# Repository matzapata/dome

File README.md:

# DOME IOT

IOT modular system to control electrical connections over Wi-Fi.
The projects consists of:
- Modular hardware built with Esp8266 and programmed with C++ that will be placed in electrical sockets
- Phone application built with React Native and expo to connect devices, control them and add family members to it. 

The figma designs are already built and can be found here: 
-  https://www.figma.com/file/vcR1ODs3bJzUiS0fuz7EVW/DOME?node-id=1102%3A9203

## Device setup

1. Create `dome-device/Secrets.h` and fill with firebase credentials

```
#define FIREBASE_HOST "..."
#define FIREBASE_RTDB_SECRET "..." 
```

2. Upload code

3. Make electrical connections and power device on

4. Reset device and keep setup button pressed

5. Connect to "DOME" network initiated by device

6. Make a `POST` to `http://192.168.4.1/set` with `ssid`, `pass`, `home_id` and `device_id` on the body of the request.

```curl
curl --location --request POST 'http://192.168.4.1/set' \
--header 'Content-Type: application/json' \
--data-raw '{
    "ssid": "...",
    "pass": "...",
    "home_id": "...",
    "device_id": "..."
}'
```

If everything is ok, device will respond with `200 "OK"`

7. That's all. Reconect your phone to your wifi and interact with the device

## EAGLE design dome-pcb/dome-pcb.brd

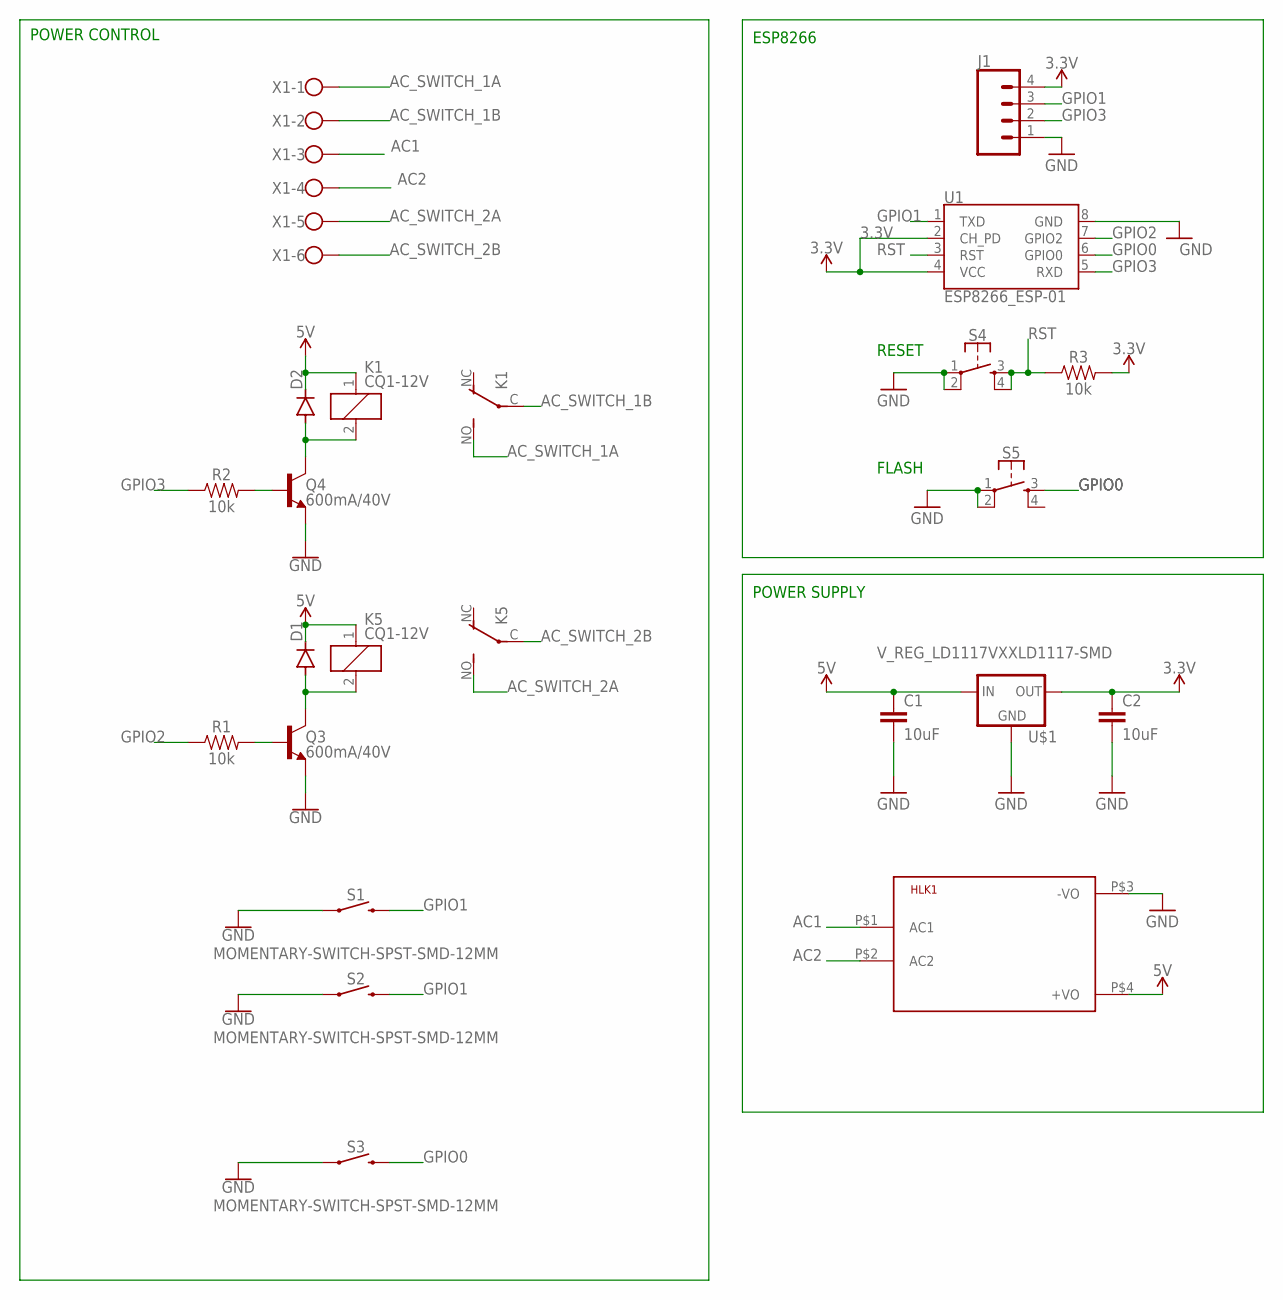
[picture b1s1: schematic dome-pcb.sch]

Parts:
C1, C2: 10uF; 0603
D1, D2: DIODE-DO-214AC; DO-214AC
HLK1: HLK-PM013W; HLK-PM01
J1: CONN_04PTH; 1X04
K1, K5: CQ1-12V; CQ1
Q3, Q4: 600mA/40V; SOT23-3
R1, R2, R3: 10k; 0603
S1, S2, S3: MOMENTARY-SWITCH-SPST-SMD-12MM; TACTILE_SWITCH_SMD_12MM
S4, S5: MOMENTARY-SWITCH-SPST-2-SMD-5.2MM; TACTILE_SWITCH_SMD_5.2MM
U1: ESP8266_ESP-01
U$1: V_REG_LD1117VXXLD1117-SMD; SOT223
X1: W237-6

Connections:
3.3V: C2.1, J1.4, R3.2, U1.2 (CH_PD), U1.4 (VCC), U$1.2 (OUT)
5V: C1.1, D1.C, D2.C, HLK1.P$4 (+VO), K1.1, K5.1, U$1.3 (IN)
AC1: HLK1.P$1 (AC1), X1.3
AC2: HLK1.P$2 (AC2), X1.4
AC_SWITCH_1A: K1.NO (S), X1.1
AC_SWITCH_1B: K1.C, X1.2
AC_SWITCH_2A: K5.NO (S), X1.5
AC_SWITCH_2B: K5.C, X1.6
GND: C1.2, C2.2, HLK1.P$3 (-VO), J1.1, Q3.2 (E), Q4.2 (E), S1.1, S2.1, S3.1, S4.1, S4.2, S5.1, S5.2, U1.8 (GND), U$1.1 (GND)
GPIO0: S3.3 (2), S5.3, U1.6 (GPIO0)
GPIO1: J1.3, S1.3 (2), S2.3 (2), U1.1 (TXD)
GPIO2: R1.1, U1.7 (GPIO2)
GPIO3: J1.2, R2.1, U1.5 (RXD)
unnamed: D2.A, K1.2, Q4.3 (C)
unnamed: Q4.1 (B), R2.2
unnamed: D1.A, K5.2, Q3.3 (C)
unnamed: Q3.1 (B), R1.2
RST: R3.1, S4.3, S4.4, U1.3 (RST)

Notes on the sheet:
FLASH
RESET
POWER CONTROL
ESP8266
POWER SUPPLY

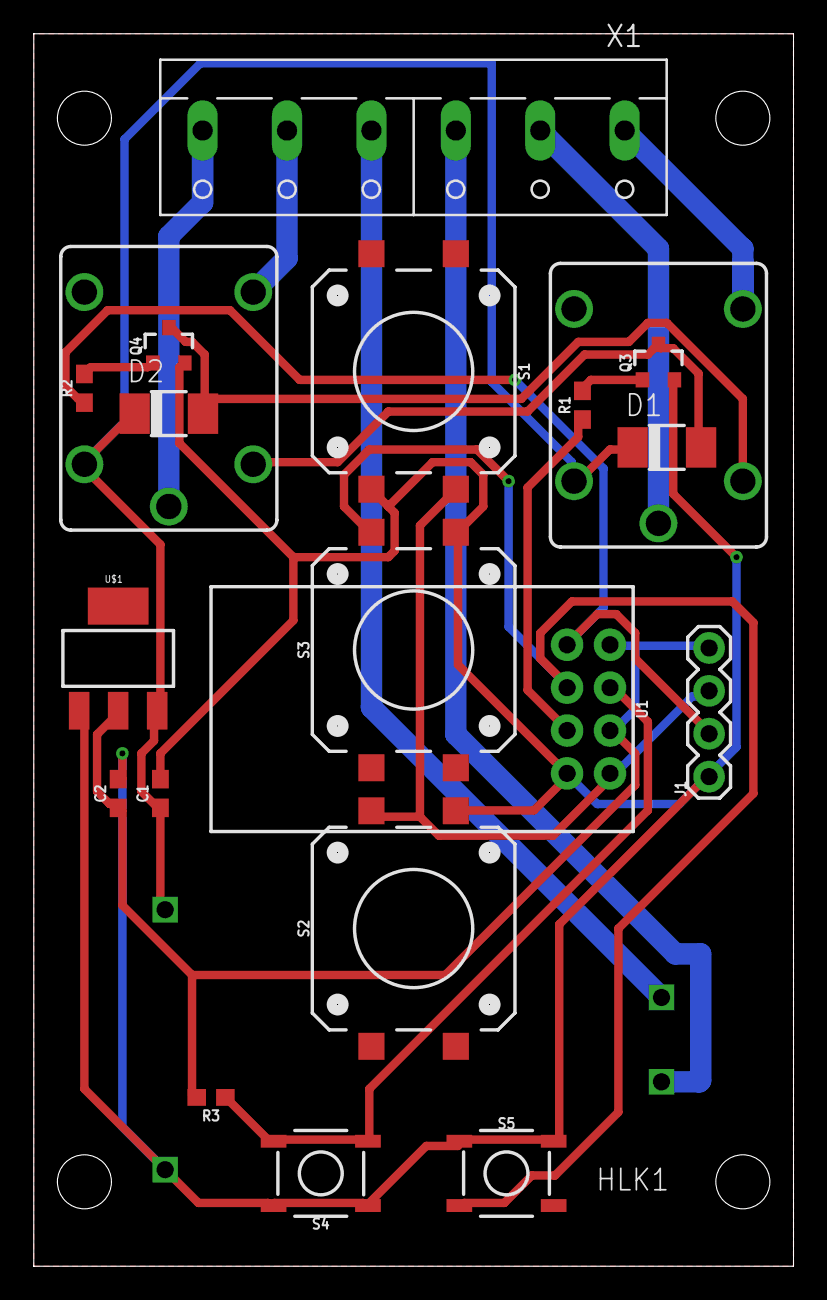
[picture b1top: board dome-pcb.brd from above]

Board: 2 copper layers, 45.0 x 73.0 mm, 21 parts (0 on the bottom side), 18 nets.

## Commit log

2022-10-07 IOT functional connection management system
2022-10-13 Firebase RTDB and buttons integration
2022-10-13 connection manager fixes
2022-10-13 Comment firebase esp version
2022-10-13 Setup NativeWind
2022-10-14 Auth pages UI
2022-10-14 Firebase integration
2022-10-15 UI Screens
2022-10-15 Initialize redux
2022-10-15 Switch Card
2022-10-15 Switches home rendering
2022-10-15 Functional prompt component
2022-10-15 Prompt component
2022-10-17 Share dome qr code generation
2022-10-17 Join dome UI
2022-10-17 Prompt styles fixes
2022-10-17 fix styles share modal
2022-10-17 Fix modal styles
2022-10-17 Reset dome confirmation
2022-10-17 Room type UI
2022-10-17 AddDevice UI screen
2022-10-17 SetupDeviceWifiNetwork UI screen
2022-10-17 Setup device screens UI
2022-10-17 Auth loading spinner
2022-10-18 Firebase redux connection. Bug in device switch
2022-10-18 Redux state refactor
2022-10-18 DeviceSwitch with rtdb sync
2022-10-18 Join dome screen fixes
2022-10-18 Password reset email firebase integration
2022-10-18 Add error alerts on signin and signup and fix settings warnings
2022-10-18 Join dome logic
2022-10-18 Admin conditional rendering
2022-10-18 Fix status bar
2022-10-18 Refactor device and fix status bar
2022-10-18 Remove google auth buttons
2022-10-18 Loading overlay redux
2022-10-18 Implement loading states for redux and auth. Navigate to home after user data fetch and not before.
2022-10-18 Secure wifi password prompt
2022-10-18 Member menu
2022-10-18 Remove console.log and fix loading rejection
2022-10-19 Update Readme cover and fix permissions bugs
2022-10-22 Modular code with macros. Listeners on new db schema
2022-10-22 Device code modularization ConnectionManager
2022-10-22 Nodes modular code with macros
2022-10-22 Hardware btn toggle and sync
2022-10-22 Altium project creation
2022-11-12 PCB v1 with ESP8266 and non SMD components
2022-11-12 Update PCB design with SMD components and a better layout
2022-11-12 PCB Schematics and board

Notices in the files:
parts and their libraries:
Connectors: Licensing: Creative Commons ShareAlike 4.0 International - https://creativecommons.org/licenses/by-sa/4.0
